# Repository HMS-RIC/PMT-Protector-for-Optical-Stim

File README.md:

View this project on [CADLAB.io](https://cadlab.io/node/999). 

# PMT-Protector-for-Optical-Stim
Protection circuit that takes a PMT shutter signal and laser stim signal. Shutter is closed when laser stim is on. Laser stim is disabled if shutter hasn't closed yet

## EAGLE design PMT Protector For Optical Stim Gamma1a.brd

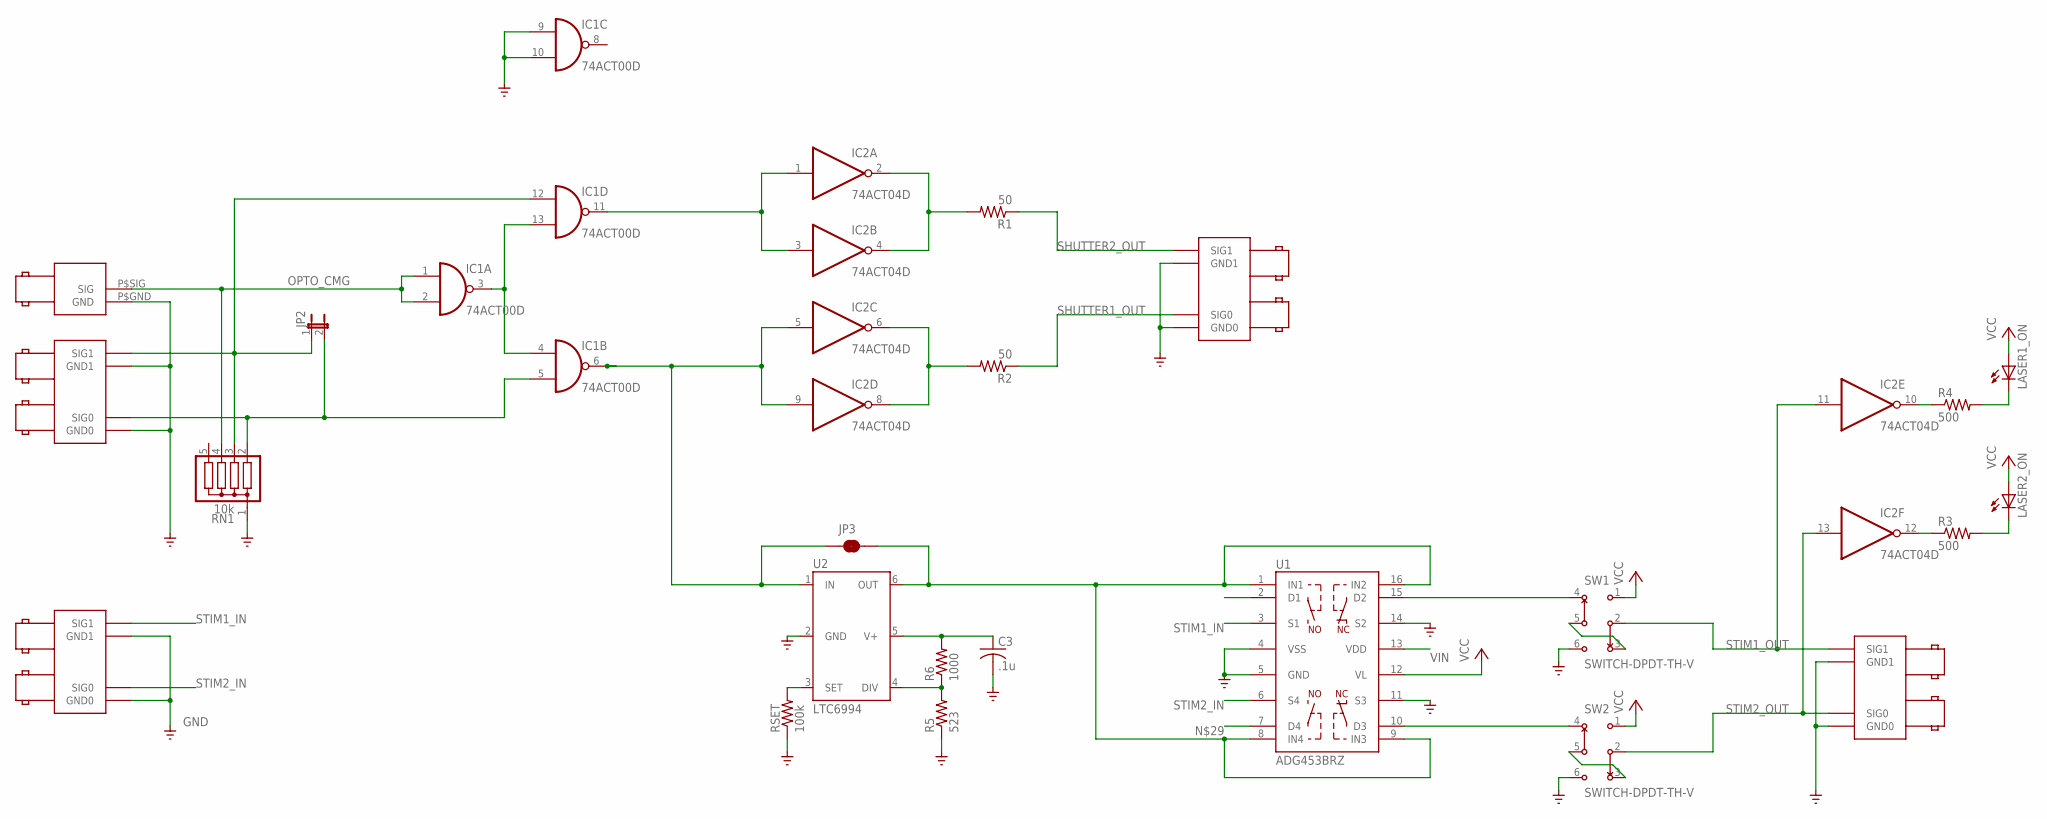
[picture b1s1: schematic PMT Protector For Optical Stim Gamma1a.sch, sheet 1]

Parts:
C3: .1u; C0805K
IC1: 74ACT00D; SO14
IC2: 74ACT04D; SO14
JP2: JP1E; JP1
JP3: JUMPER-SMT_2_NC_TRACE_SILK; SMT-JUMPER_2_NC_TRACE_SILK
LASER1_ON, LASER2_ON: LED5MM
OPTO_CMG: BNC_RIGHT_ANGLE
R1, R2: 50; R0805
R3, R4: 500; R0805
R5: 523; R0805
R6: 1000; R0805
RN1: 10k; SIL5
RSET: 100k; R0805
SHTR_IN: BNC_RIGHT_ANGLE_DOUBLE
SHTR_OUT: BNC_RIGHT_ANGLE_DOUBLE
STIM_IN: BNC_RIGHT_ANGLE_DOUBLE
STIM_OUT: BNC_RIGHT_ANGLE_DOUBLE
SW1, SW2: SWITCH-DPDT-TH-V; SWITCH-DPDT
U1: ADG453BRZ; SO16
U2: LTC6994; SOT23-6

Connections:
GND: C3.2, IC1.9 (I0), IC1.10 (I1), OPTO_CMG.P$GND (GND), R5.1, RN1.1, RSET.1, SHTR_IN.P$GND0 (GND0), SHTR_IN.P$GND1 (GND1), SHTR_OUT.P$GND0 (GND0), SHTR_OUT.P$GND1 (GND1), STIM_IN.P$GND0 (GND0), STIM_IN.P$GND1 (GND1), STIM_OUT.P$GND0 (GND0), STIM_OUT.P$GND1 (GND1), SW1.6, SW2.6, U1.4 (VSS), U1.5 (GND), U1.11 (S3), U1.14 (S2), U2.2 (GND); also elsewhere on the board
unnamed: IC1.12 (I0), JP2.1, RN1.3, SHTR_IN.P$SIG1 (SIG1)
unnamed: IC2.12 (O), R3.1
unnamed: IC1.6 (O), IC2.5 (I), IC2.9 (I), JP3.1, U2.1 (IN)
unnamed: IC2.2 (O), IC2.4 (O), R1.2
unnamed: IC2.10 (O), R4.1
unnamed: LASER1_ON.K (C), R4.2
unnamed: LASER2_ON.K (C), R3.2
unnamed: SW2.3, SW2.5
unnamed: IC1.11 (O), IC2.1 (I), IC2.3 (I)
unnamed: IC2.6 (O), IC2.8 (O), R2.2
unnamed: IC1.3 (O), IC1.4 (I0), IC1.13 (I1)
unnamed: SW2.4, U1.7 (D4), U1.10 (D3)
unnamed: JP3.2, U1.1 (IN1), U1.8 (IN4), U1.9 (IN3), U1.16 (IN2), U2.6 (OUT)
unnamed: SW1.3, SW1.5
unnamed: SW1.4, U1.2 (D1), U1.15 (D2)
unnamed: R5.2, R6.1, U2.4 (DIV)
unnamed: RSET.2, U2.3 (SET)
OPTO_CMG: IC1.1 (I0), IC1.2 (I1), OPTO_CMG.P$SIG (SIG), RN1.4
SHUTTER1_OUT: R2.1, SHTR_OUT.P$SIG0 (SIG0)
SHUTTER2_OUT: R1.1, SHTR_OUT.P$SIG1 (SIG1)
SHUTTER_IN: IC1.5 (I1), JP2.2, RN1.2, SHTR_IN.P$SIG0 (SIG0)
STIM1_IN: STIM_IN.P$SIG1 (SIG1), U1.3 (S1)
STIM1_OUT: IC2.11 (I), STIM_OUT.P$SIG1 (SIG1), SW1.2
STIM2_IN: STIM_IN.P$SIG0 (SIG0), U1.6 (S4)
STIM2_OUT: IC2.13 (I), STIM_OUT.P$SIG0 (SIG0), SW2.2
VCC: LASER1_ON.A, LASER2_ON.A, SW1.1, SW2.1, U1.12 (VL); also elsewhere on the board
VCC2: C3.1, R6.2, U2.5 (V+)
VIN: U1.13 (VDD); also elsewhere on the board

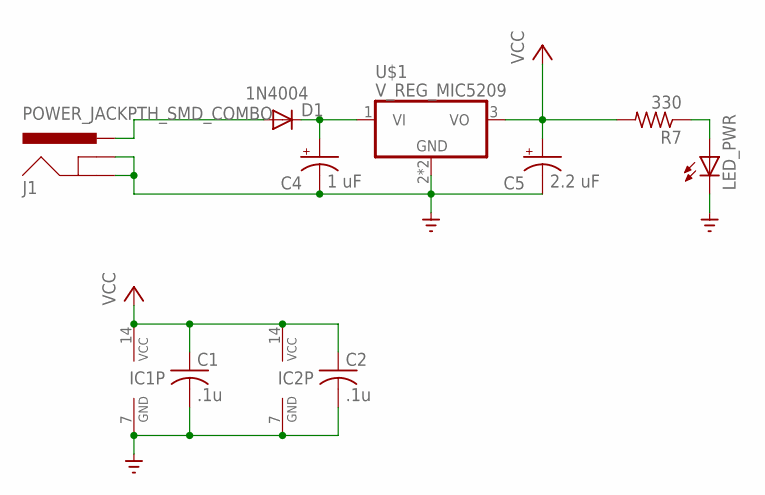
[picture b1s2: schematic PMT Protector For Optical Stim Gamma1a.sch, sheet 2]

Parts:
C1, C2: .1u; C0805K
C4: 1 uF; E2,5-5
C5: 2.2 uF; E2,5-5
D1: 1N4004; DO41-10
IC1: 74ACT00D; SO14
IC2: 74ACT04D; SO14
J1: POWER_JACKPTH_SMD_COMBO; POWER_JACK_COMBO
LED_PWR: LED5MM
R7: 330; R0805
U$1: V_REG_MIC5209; SOT-223

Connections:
GND: C1.2, C2.2, C4.-, C5.-, IC1.7 (GND), IC2.7 (GND), J1.GND (GNDBREAK), J1.GND@1 (GND), LED_PWR.K (C), U$1.2 (GND), U$1.4 (GND); also elsewhere on the board
unnamed: D1.A, J1.POWER (PWR)
unnamed: LED_PWR.A, R7.1
VCC: C1.1, C2.1, C5.+, IC1.14 (VCC), IC2.14 (VCC), R7.2, U$1.3 (VO); also elsewhere on the board
VIN: C4.+, D1.C, U$1.1 (VI); also elsewhere on the board

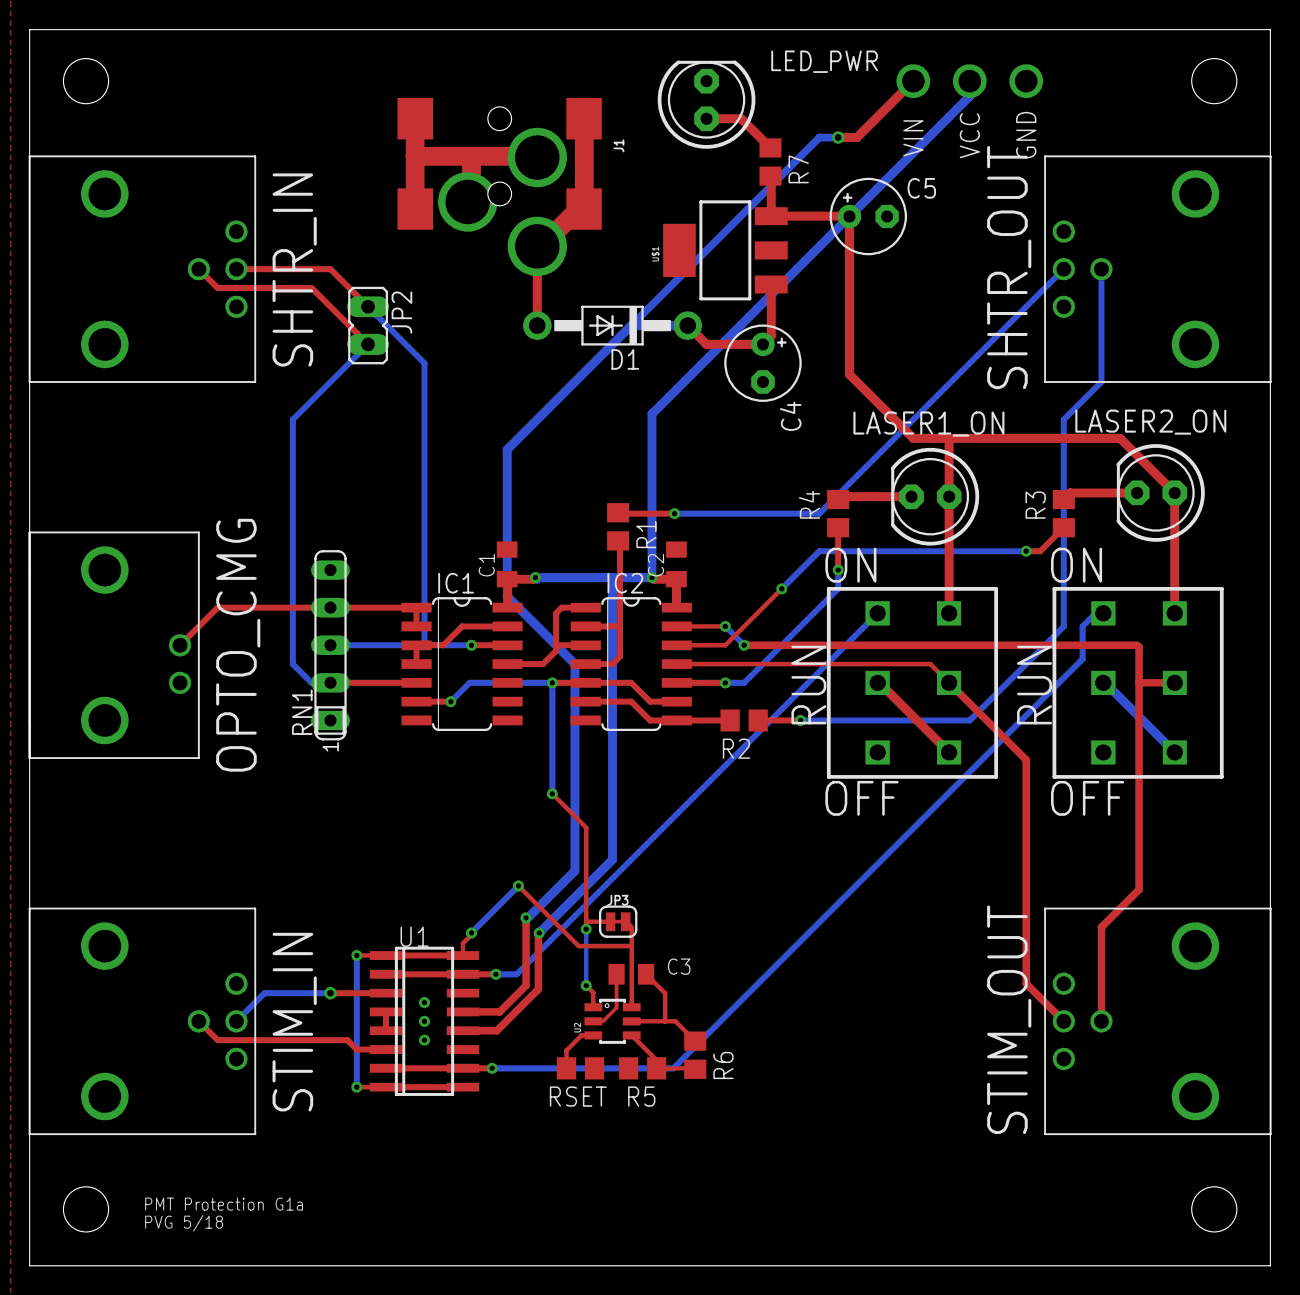
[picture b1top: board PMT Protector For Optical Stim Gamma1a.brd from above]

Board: 2 copper layers, 83.8 x 83.5 mm, 33 parts (0 on the bottom side), 31 nets.

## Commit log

2018-05-08 Backlink to CADLAB.io has been added.

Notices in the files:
parts and their libraries:
SparkFun-Connectors: Licensing: Creative Commons ShareAlike 4.0 International - https://creativecommons.org/licenses/by-sa/4.0
